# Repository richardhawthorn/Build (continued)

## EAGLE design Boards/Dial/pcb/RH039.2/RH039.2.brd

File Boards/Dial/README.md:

### Description

Dial board for use in build system

### Features

- Rotary encoder dial
- ATtiny44 processor
- DIL switch for 4 board addresses
- i2c communication with base
- 3.3v operation
- Surface mount

### License

This work is licensed under a Creative Commons Attribution-ShareAlike 4.0 International License.

<br />
Designed by <a xmlns:cc="http://creativecommons.org/ns#" href="http://www.richardhawthorn.com" property="cc:attributionName" rel="cc:attributionURL" target="_blank">Richard Hawthorn</a><br />
<a rel="license" href="http://creativecommons.org/licenses/by-sa/4.0/" target="_blank">View License</a>

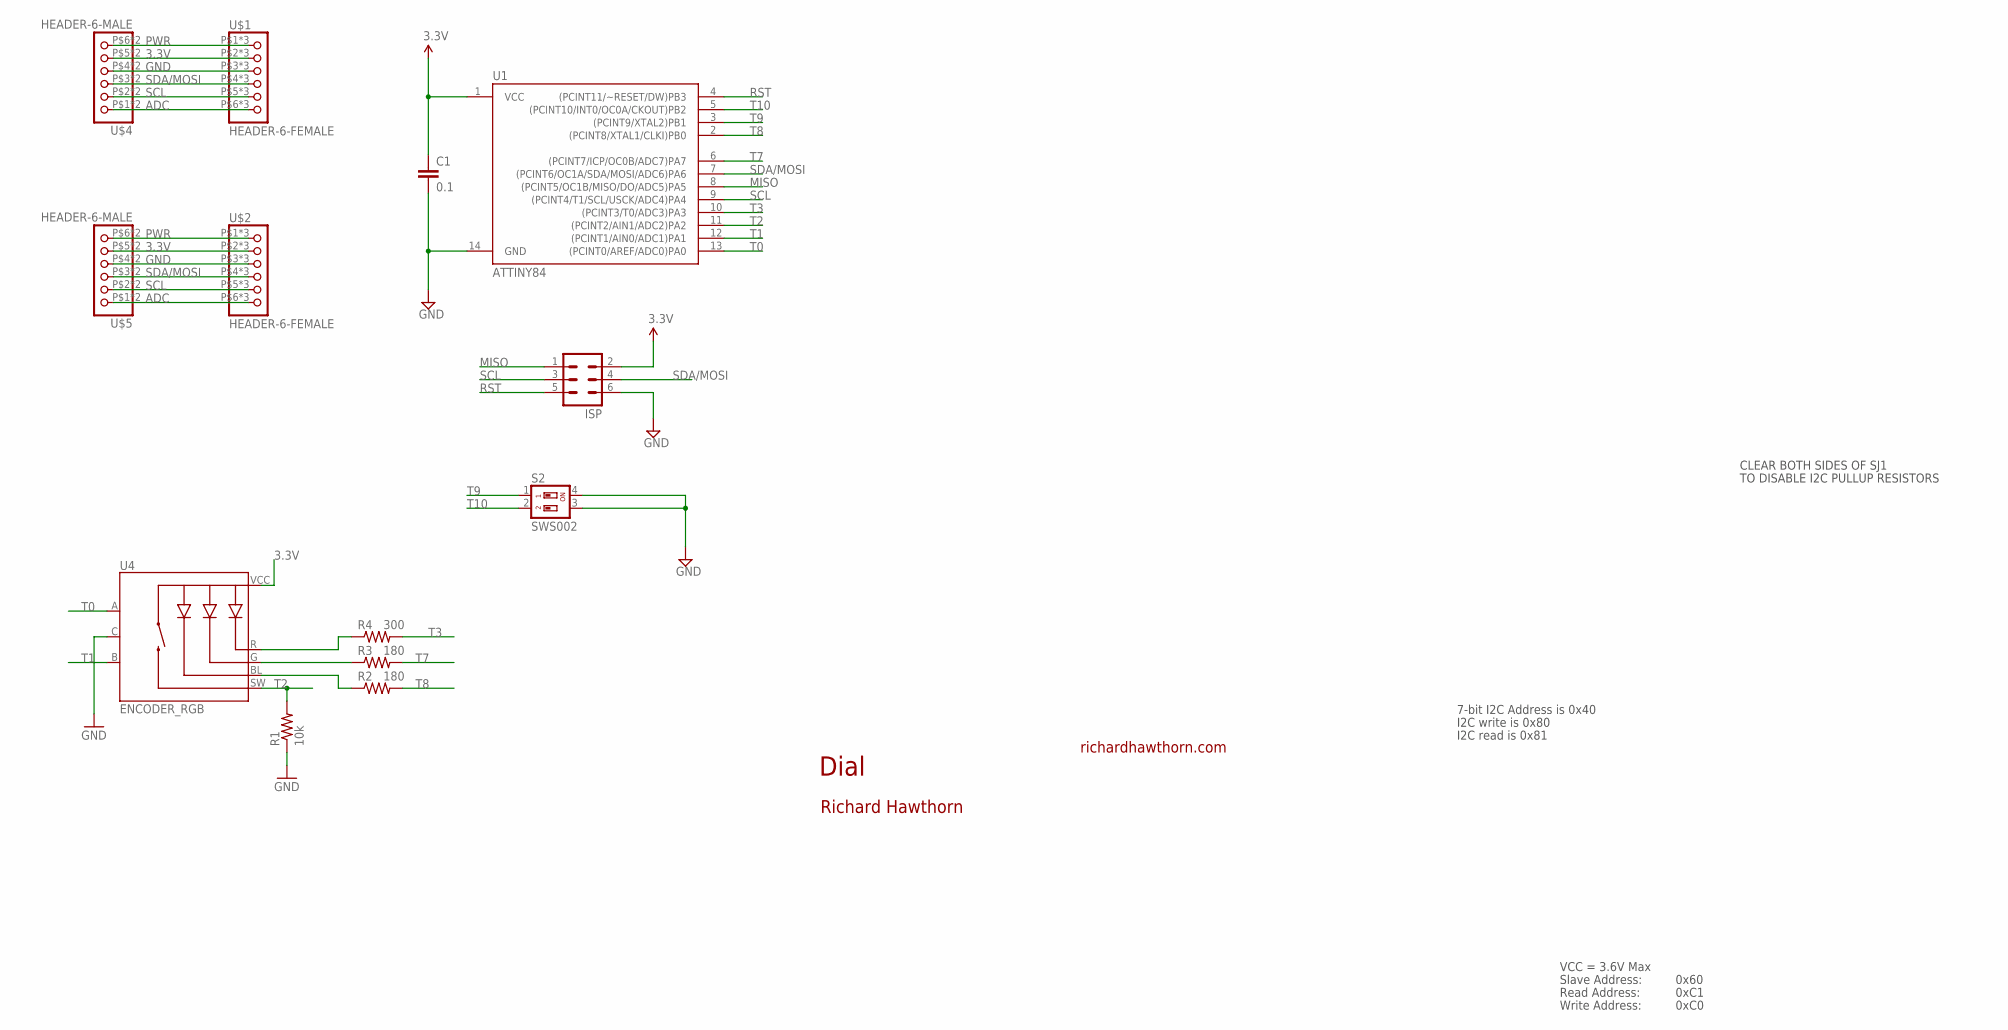
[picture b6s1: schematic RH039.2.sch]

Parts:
C1: 0.1; 0603-CAP
ISP: MA03-2
R1: 10k; 0402-RES
R2, R3: 180; 0402-RES
R4: 300; 0402-RES
S2: SWS002; SMS-002
U1: ATTINY84; SO14
U4: ENCODER_RGB; ENCODER_LED_RGB
U$1, U$2: HEADER-6-FEMALE; 2MMHEADER6
U$4, U$5: HEADER-6-MALE; 2MMHEADERPIN6

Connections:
3.3V: C1.1, ISP.2, U1.1 (VCC), U4.VCC, U$1.P$2 (2), U$1.P$10 (2), U$1.P$18 (2), U$2.P$2 (2), U$2.P$10 (2), U$2.P$18 (2), U$4.P$5 (5), U$4.P$13 (5), U$5.P$5 (5), U$5.P$13 (5)
ADC: U$1.P$6 (6), U$1.P$14 (6), U$1.P$22 (6), U$2.P$6 (6), U$2.P$14 (6), U$2.P$22 (6), U$4.P$1 (1), U$4.P$9 (1), U$5.P$1 (1), U$5.P$9 (1)
GND: C1.2, ISP.6, R1.1, S2.3, S2.4, U1.14 (GND), U4.C, U$1.P$3 (3), U$1.P$11 (3), U$1.P$19 (3), U$2.P$3 (3), U$2.P$11 (3), U$2.P$19 (3), U$4.P$4 (4), U$4.P$12 (4), U$5.P$4 (4), U$5.P$12 (4)
LED-B: R2.1, U4.BL
LED-G: R3.1, U4.G
LED-R: R4.1, U4.R
MISO: ISP.1, U1.8 ((PCINT5/OC1B/MISO/DO/ADC5)PA5)
PWR: U$1.P$1 (1), U$1.P$9 (1), U$1.P$17 (1), U$2.P$1 (1), U$2.P$9 (1), U$2.P$17 (1), U$4.P$6 (6), U$4.P$14 (6), U$5.P$6 (6), U$5.P$14 (6)
RST: ISP.5, U1.4 ((PCINT11/~RESET/DW)PB3)
SCL: ISP.3, U1.9 ((PCINT4/T1/SCL/USCK/ADC4)PA4), U$1.P$5 (5), U$1.P$13 (5), U$1.P$21 (5), U$2.P$5 (5), U$2.P$13 (5), U$2.P$21 (5), U$4.P$2 (2), U$4.P$10 (2), U$5.P$2 (2), U$5.P$10 (2)
SDA/MOSI: ISP.4, U1.7 ((PCINT6/OC1A/SDA/MOSI/ADC6)PA6), U$1.P$4 (4), U$1.P$12 (4), U$1.P$20 (4), U$2.P$4 (4), U$2.P$12 (4), U$2.P$20 (4), U$4.P$3 (3), U$4.P$11 (3), U$5.P$3 (3), U$5.P$11 (3)
T0: U1.13 ((PCINT0/AREF/ADC0)PA0), U4.A
T1: U1.12 ((PCINT1/AIN0/ADC1)PA1), U4.B
T2: R1.2, U1.11 ((PCINT2/AIN1/ADC2)PA2), U4.SW
T3: R4.2, U1.10 ((PCINT3/T0/ADC3)PA3)
T7: R3.2, U1.6 ((PCINT7/ICP/OC0B/ADC7)PA7)
T8: R2.2, U1.2 ((PCINT8/XTAL1/CLKI)PB0)
T9: S2.1, U1.3 ((PCINT9/XTAL2)PB1)
T10: S2.2, U1.5 ((PCINT10/INT0/OC0A/CKOUT)PB2)

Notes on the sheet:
Dial
richardhawthorn.com
Richard Hawthorn
CLEAR BOTH SIDES OF SJ1
TO DISABLE I2C PULLUP RESISTORS
7-bit I2C Address is 0x40
I2C write is 0x80
I2C read is 0x81
VCC = 3.6V Max
Read Address:
Write Address:
Slave Address:
0x60
0xC1
0xC0

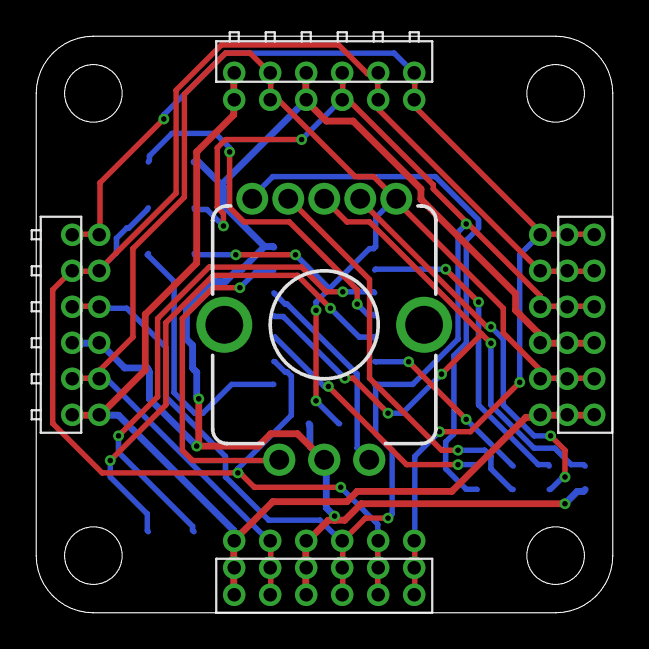
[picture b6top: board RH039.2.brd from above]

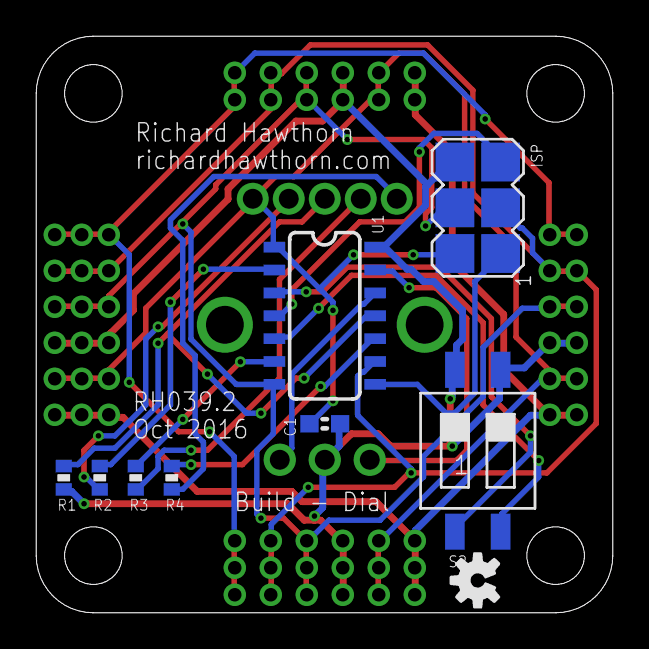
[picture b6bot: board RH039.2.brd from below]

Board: 2 copper layers, 32.0 x 32.0 mm, 14 parts (9 on the bottom side), 19 nets.

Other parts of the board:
U$3: OSHW-LOGO-S

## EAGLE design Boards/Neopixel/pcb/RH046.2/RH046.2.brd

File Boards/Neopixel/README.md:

### Description

Neopixel board for use in build system

### Features

- 2x2 Neopixels
- ATtiny44 processor
- DIL switch for 8 board addresses
- i2c communication with base
- 3.3v operation
- Surface mount

### License

This work is licensed under a Creative Commons Attribution-ShareAlike 4.0 International License.

<br />
Designed by <a xmlns:cc="http://creativecommons.org/ns#" href="http://www.richardhawthorn.com" property="cc:attributionName" rel="cc:attributionURL" target="_blank">Richard Hawthorn</a><br />
<a rel="license" href="http://creativecommons.org/licenses/by-sa/4.0/" target="_blank">View License</a>

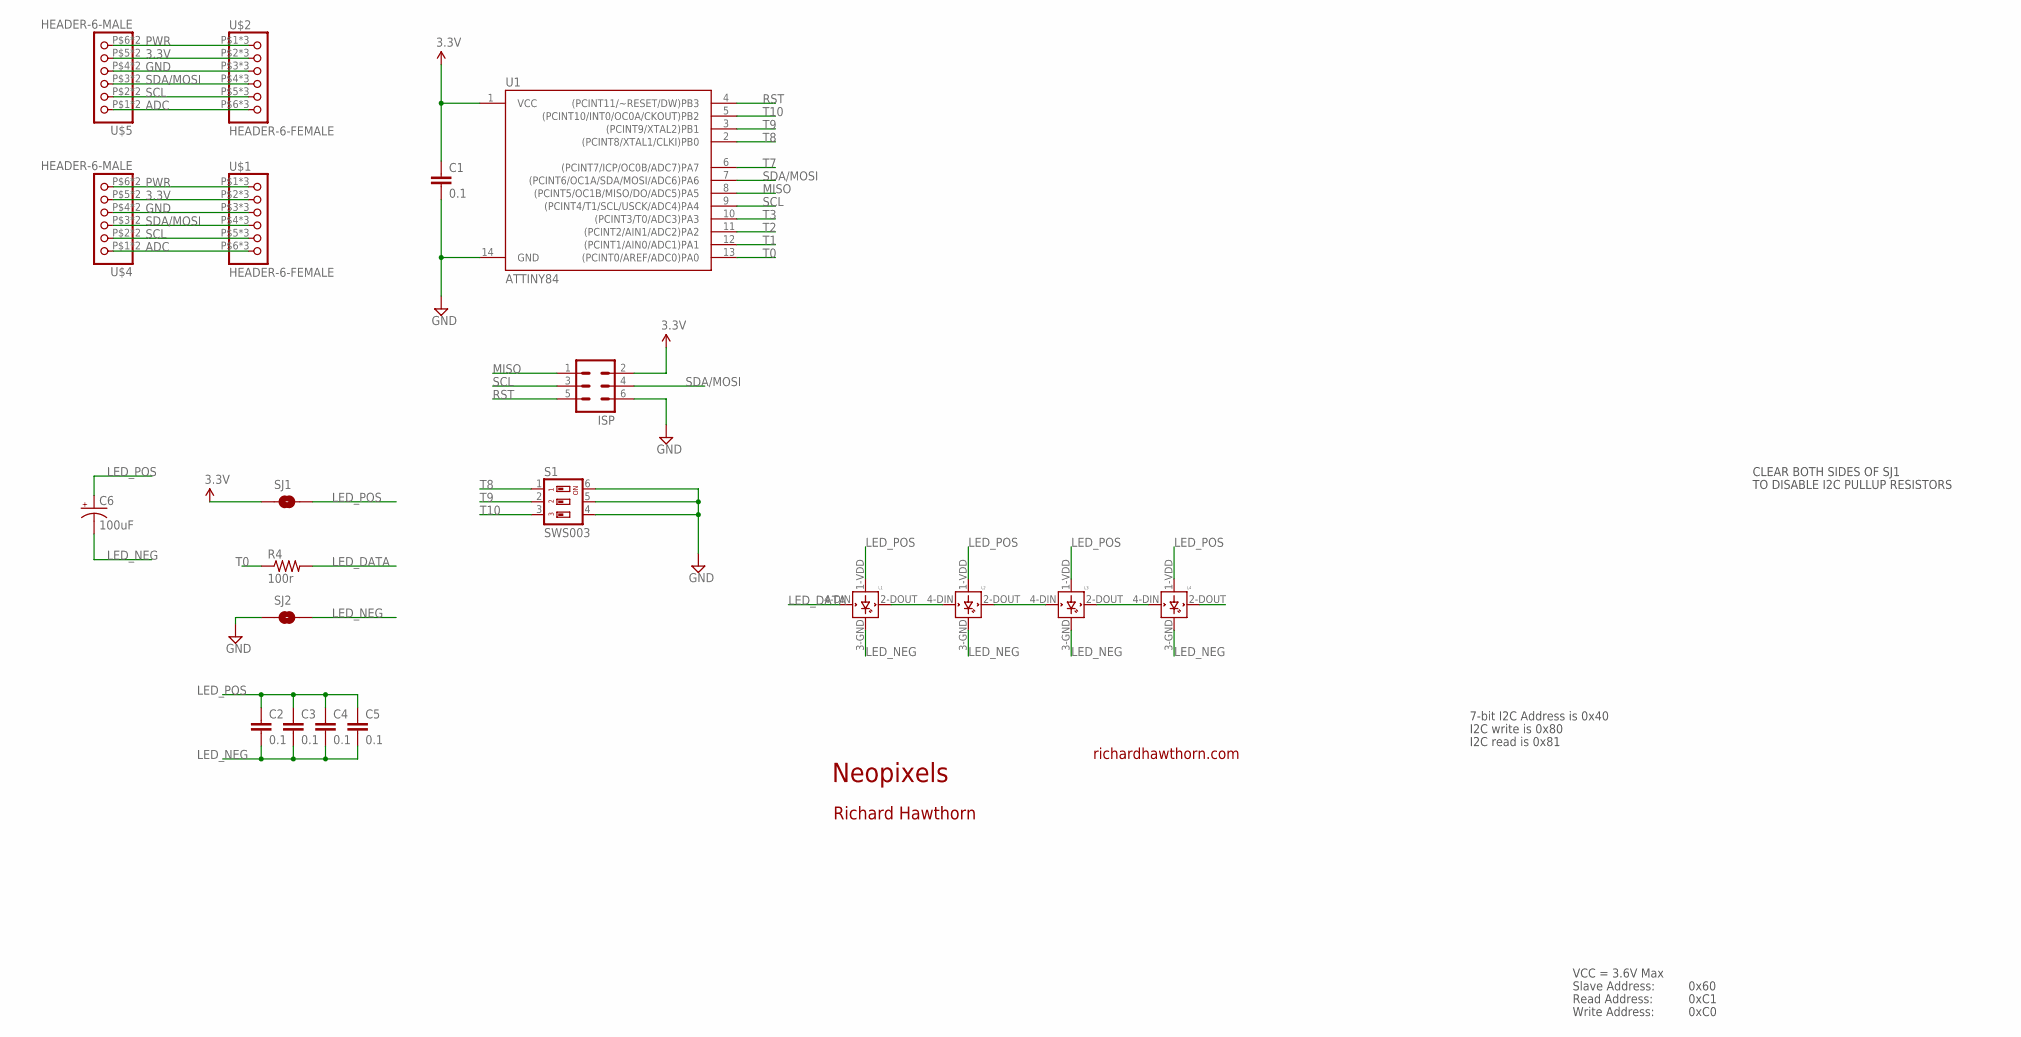
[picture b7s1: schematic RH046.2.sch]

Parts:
C1, C2, C3, C4, C5: 0.1; 0603-CAP
C6: 100uF; EIA7343
ISP: MA03-2
L1, L2, L3, L4: WS2812B
R4: 100r; 0603-RES
S1: SWS003; SMS-003
SJ1, SJ2: SOLDERJUMPERNO; SJ_2S-NO
U1: ATTINY84; SO14
U$1, U$2: HEADER-6-FEMALE; 2MMHEADER6
U$4, U$5: HEADER-6-MALE; 2MMHEADERPIN6

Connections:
3.3V: C1.1, ISP.2, SJ1.1, U1.1 (VCC), U$1.P$2 (2), U$1.P$10 (2), U$1.P$18 (2), U$2.P$2 (2), U$2.P$10 (2), U$2.P$18 (2), U$4.P$5 (5), U$4.P$13 (5), U$5.P$5 (5), U$5.P$13 (5)
ADC: U$1.P$6 (6), U$1.P$14 (6), U$1.P$22 (6), U$2.P$6 (6), U$2.P$14 (6), U$2.P$22 (6), U$4.P$1 (1), U$4.P$9 (1), U$5.P$1 (1), U$5.P$9 (1)
GND: C1.2, ISP.6, S1.4, S1.5, S1.6, SJ2.1, U1.14 (GND), U$1.P$3 (3), U$1.P$11 (3), U$1.P$19 (3), U$2.P$3 (3), U$2.P$11 (3), U$2.P$19 (3), U$4.P$4 (4), U$4.P$12 (4), U$5.P$4 (4), U$5.P$12 (4)
LED-OUT-1: L1.2-DOUT (DOUT), L2.4-DIN (DIN)
LED-OUT-2: L3.2-DOUT (DOUT), L4.4-DIN (DIN)
LED-OUT-3: L4.2-DOUT (DOUT)
LED_DATA: L1.4-DIN (DIN), R4.2
LED_NEG: C2.2, C3.2, C4.2, C5.2, C6.C (-), L1.3-GND (GND), L2.3-GND (GND), L3.3-GND (GND), L4.3-GND (GND), SJ2.2
LED_POS: C2.1, C3.1, C4.1, C5.1, C6.A (+), L1.1-VDD (VDD), L2.1-VDD (VDD), L3.1-VDD (VDD), L4.1-VDD (VDD), SJ1.2
MISO: ISP.1, U1.8 ((PCINT5/OC1B/MISO/DO/ADC5)PA5)
unnamed: L2.2-DOUT (DOUT), L3.4-DIN (DIN)
PWR: U$1.P$1 (1), U$1.P$9 (1), U$1.P$17 (1), U$2.P$1 (1), U$2.P$9 (1), U$2.P$17 (1), U$4.P$6 (6), U$4.P$14 (6), U$5.P$6 (6), U$5.P$14 (6)
RST: ISP.5, U1.4 ((PCINT11/~RESET/DW)PB3)
SCL: ISP.3, U1.9 ((PCINT4/T1/SCL/USCK/ADC4)PA4), U$1.P$5 (5), U$1.P$13 (5), U$1.P$21 (5), U$2.P$5 (5), U$2.P$13 (5), U$2.P$21 (5), U$4.P$2 (2), U$4.P$10 (2), U$5.P$2 (2), U$5.P$10 (2)
SDA/MOSI: ISP.4, U1.7 ((PCINT6/OC1A/SDA/MOSI/ADC6)PA6), U$1.P$4 (4), U$1.P$12 (4), U$1.P$20 (4), U$2.P$4 (4), U$2.P$12 (4), U$2.P$20 (4), U$4.P$3 (3), U$4.P$11 (3), U$5.P$3 (3), U$5.P$11 (3)
T0: R4.1, U1.13 ((PCINT0/AREF/ADC0)PA0)
T1: U1.12 ((PCINT1/AIN0/ADC1)PA1)
T2: U1.11 ((PCINT2/AIN1/ADC2)PA2)
T3: U1.10 ((PCINT3/T0/ADC3)PA3)
T7: U1.6 ((PCINT7/ICP/OC0B/ADC7)PA7)
T8: S1.1, U1.2 ((PCINT8/XTAL1/CLKI)PB0)
T9: S1.2, U1.3 ((PCINT9/XTAL2)PB1)
T10: S1.3, U1.5 ((PCINT10/INT0/OC0A/CKOUT)PB2)

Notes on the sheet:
Neopixels
richardhawthorn.com
Richard Hawthorn
CLEAR BOTH SIDES OF SJ1
TO DISABLE I2C PULLUP RESISTORS
7-bit I2C Address is 0x40
I2C write is 0x80
I2C read is 0x81
VCC = 3.6V Max
Read Address:
Write Address:
Slave Address:
0x60
0xC1
0xC0

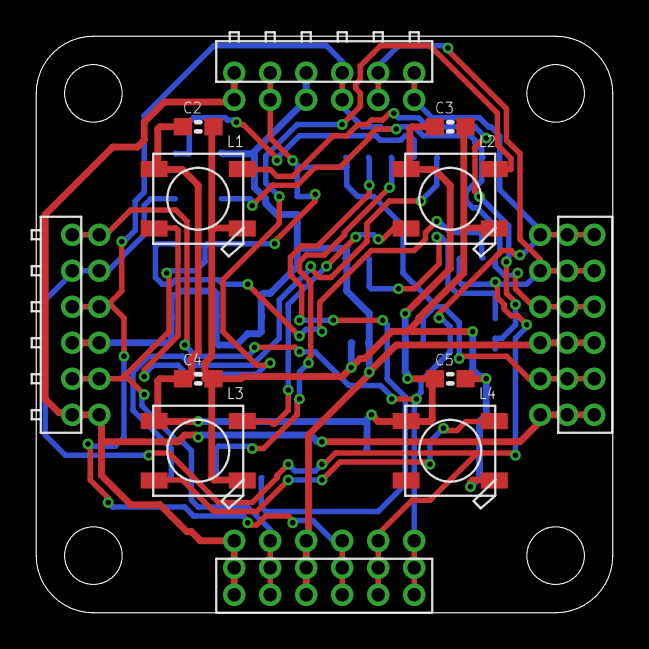
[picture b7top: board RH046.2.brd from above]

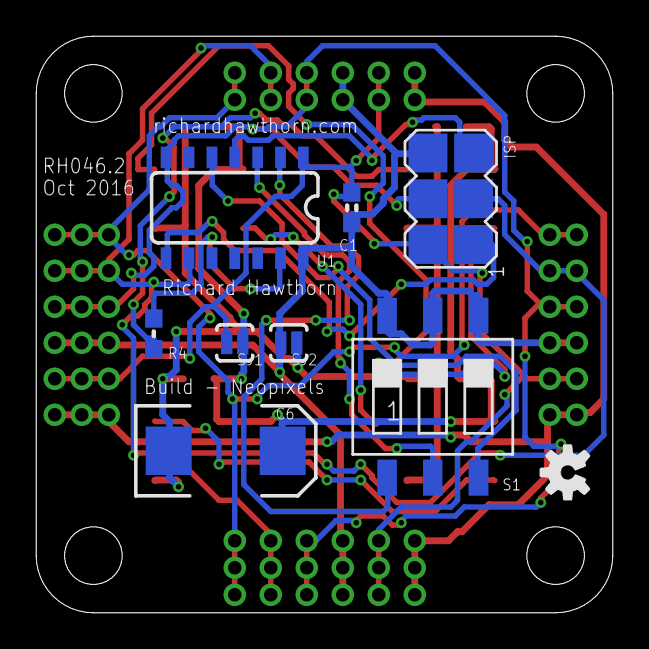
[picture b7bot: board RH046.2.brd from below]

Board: 2 copper layers, 32.0 x 32.0 mm, 21 parts (9 on the bottom side), 18 nets.

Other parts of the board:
U$3: OSHW-LOGO-S

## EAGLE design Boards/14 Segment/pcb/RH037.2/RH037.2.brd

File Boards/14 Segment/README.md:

### Description

14 segment LED screen for use in build system

### Features

- 14 Segment LED screen
- HT16K33 LED driver
- DIL switch for 8 board addresses
- i2c communication with base
- 3.3v operation
- Surface mount

### License

This work is licensed under a Creative Commons Attribution-ShareAlike 4.0 International License.

<br />
Designed by <a xmlns:cc="http://creativecommons.org/ns#" href="http://www.richardhawthorn.com" property="cc:attributionName" rel="cc:attributionURL" target="_blank">Richard Hawthorn</a><br />
<a rel="license" href="http://creativecommons.org/licenses/by-sa/4.0/" target="_blank">View License</a>

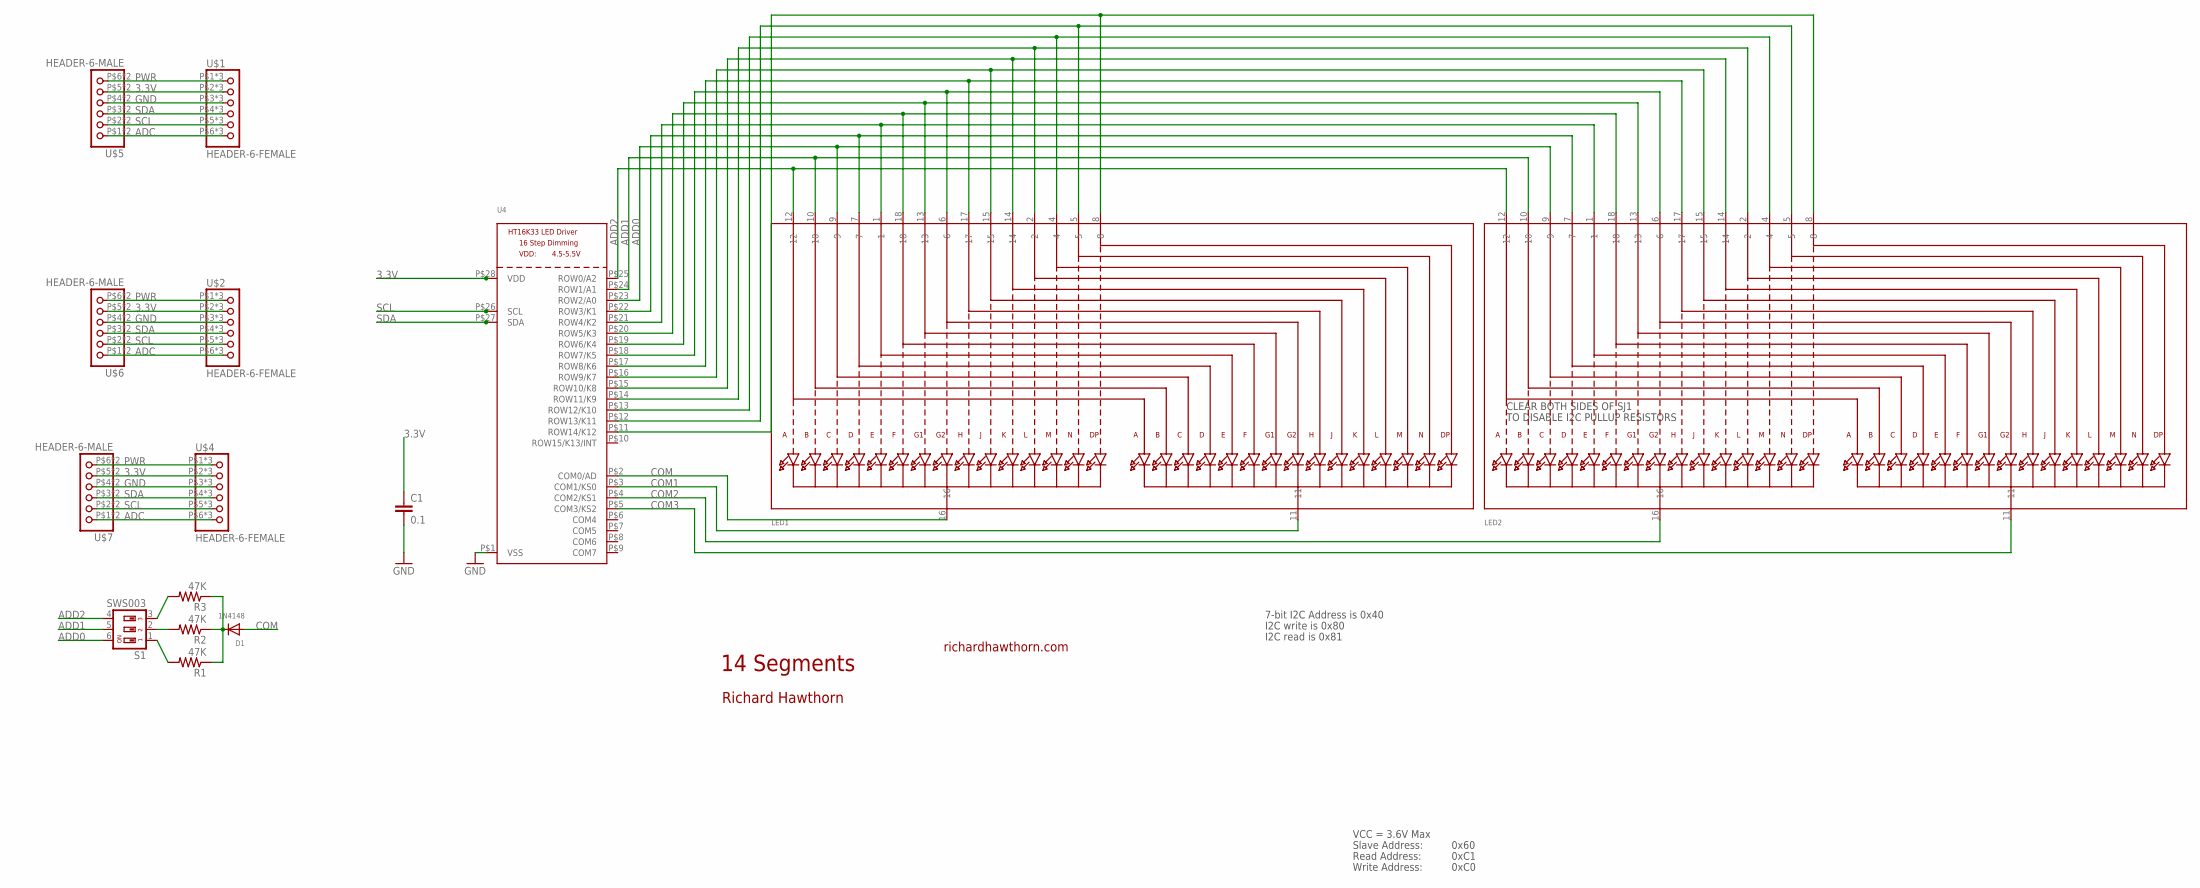
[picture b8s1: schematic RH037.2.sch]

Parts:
C1: 0.1; 0603-CAP
D1: 1N4148; SOD-323F
LED1, LED2: DISP_SEGMENT_STARBURST_DUAL_COMMONCATHODE; SEGMENT_STARTBUST_DUAL_KWA-541CBB
R1, R2, R3: 47K; R0805
S1: SWS003; SMS-003
U4: HT16K33_SOP28; SOP28_300MIL
U$1, U$2, U$4: HEADER-6-FEMALE; 2MMHEADER6
U$5, U$6, U$7: HEADER-6-MALE; 2MMHEADERPIN6

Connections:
3.3V: C1.1, U4.P$28 (VDD), U$1.P$2 (2), U$1.P$10 (2), U$1.P$18 (2), U$2.P$2 (2), U$2.P$10 (2), U$2.P$18 (2), U$4.P$2 (2), U$4.P$10 (2), U$4.P$18 (2), U$5.P$5 (5), U$5.P$13 (5), U$6.P$5 (5), U$6.P$13 (5), U$7.P$5 (5), U$7.P$13 (5)
ADC: U$1.P$6 (6), U$1.P$14 (6), U$1.P$22 (6), U$2.P$6 (6), U$2.P$14 (6), U$2.P$22 (6), U$4.P$6 (6), U$4.P$14 (6), U$4.P$22 (6), U$5.P$1 (1), U$5.P$9 (1), U$6.P$1 (1), U$6.P$9 (1), U$7.P$1 (1), U$7.P$9 (1)
ADD0: LED1.9, LED2.9, S1.6, U4.P$23 (ROW2/A0)
ADD1: LED1.10, LED2.10, S1.5, U4.P$24 (ROW1/A1)
ADD2: LED1.12, LED2.12, S1.4, U4.P$25 (ROW0/A2)
COM: D1.A, LED1.16, U4.P$2 (COM0/AD)
COM1: LED1.11, U4.P$3 (COM1/KS0)
COM2: LED2.16, U4.P$4 (COM2/KS1)
COM3: LED2.11, U4.P$5 (COM3/KS2)
GND: C1.2, U4.P$1 (VSS), U$1.P$3 (3), U$1.P$11 (3), U$1.P$19 (3), U$2.P$3 (3), U$2.P$11 (3), U$2.P$19 (3), U$4.P$3 (3), U$4.P$11 (3), U$4.P$19 (3), U$5.P$4 (4), U$5.P$12 (4), U$6.P$4 (4), U$6.P$12 (4), U$7.P$4 (4), U$7.P$12 (4)
unnamed: R3.2, S1.3
unnamed: D1.C, R1.1, R2.1, R3.1
unnamed: R1.2, S1.1
unnamed: R2.2, S1.2
unnamed: LED1.7, LED2.7, U4.P$22 (ROW3/K1)
unnamed: LED1.1, LED2.1, U4.P$21 (ROW4/K2)
unnamed: LED1.18, LED2.18, U4.P$20 (ROW5/K3)
unnamed: LED1.13, LED2.13, U4.P$19 (ROW6/K4)
unnamed: LED1.6, LED2.6, U4.P$18 (ROW7/K5)
unnamed: LED1.17, LED2.17, U4.P$17 (ROW8/K6)
unnamed: LED1.15, LED2.15, U4.P$16 (ROW9/K7)
unnamed: LED1.14, LED2.14, U4.P$15 (ROW10/K8)
unnamed: LED1.2, LED2.2, U4.P$14 (ROW11/K9)
unnamed: LED1.4, LED2.4, U4.P$13 (ROW12/K10)
unnamed: LED1.5, LED2.5, U4.P$12 (ROW13/K11)
unnamed: LED1.8, LED2.8, U4.P$11 (ROW14/K12)
PWR: U$1.P$1 (1), U$1.P$9 (1), U$1.P$17 (1), U$2.P$1 (1), U$2.P$9 (1), U$2.P$17 (1), U$4.P$1 (1), U$4.P$9 (1), U$4.P$17 (1), U$5.P$6 (6), U$5.P$14 (6), U$6.P$6 (6), U$6.P$14 (6), U$7.P$6 (6), U$7.P$14 (6)
SCL: U4.P$26 (SCL), U$1.P$5 (5), U$1.P$13 (5), U$1.P$21 (5), U$2.P$5 (5), U$2.P$13 (5), U$2.P$21 (5), U$4.P$5 (5), U$4.P$13 (5), U$4.P$21 (5), U$5.P$2 (2), U$5.P$10 (2), U$6.P$2 (2), U$6.P$10 (2), U$7.P$2 (2), U$7.P$10 (2)
SDA: U4.P$27 (SDA), U$1.P$4 (4), U$1.P$12 (4), U$1.P$20 (4), U$2.P$4 (4), U$2.P$12 (4), U$2.P$20 (4), U$4.P$4 (4), U$4.P$12 (4), U$4.P$20 (4), U$5.P$3 (3), U$5.P$11 (3), U$6.P$3 (3), U$6.P$11 (3), U$7.P$3 (3), U$7.P$11 (3)

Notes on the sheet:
14 Segments
richardhawthorn.com
Richard Hawthorn
CLEAR BOTH SIDES OF SJ1
TO DISABLE I2C PULLUP RESISTORS
7-bit I2C Address is 0x40
I2C write is 0x80
I2C read is 0x81
VCC = 3.6V Max
Read Address:
Write Address:
Slave Address:
0x60
0xC1
0xC0

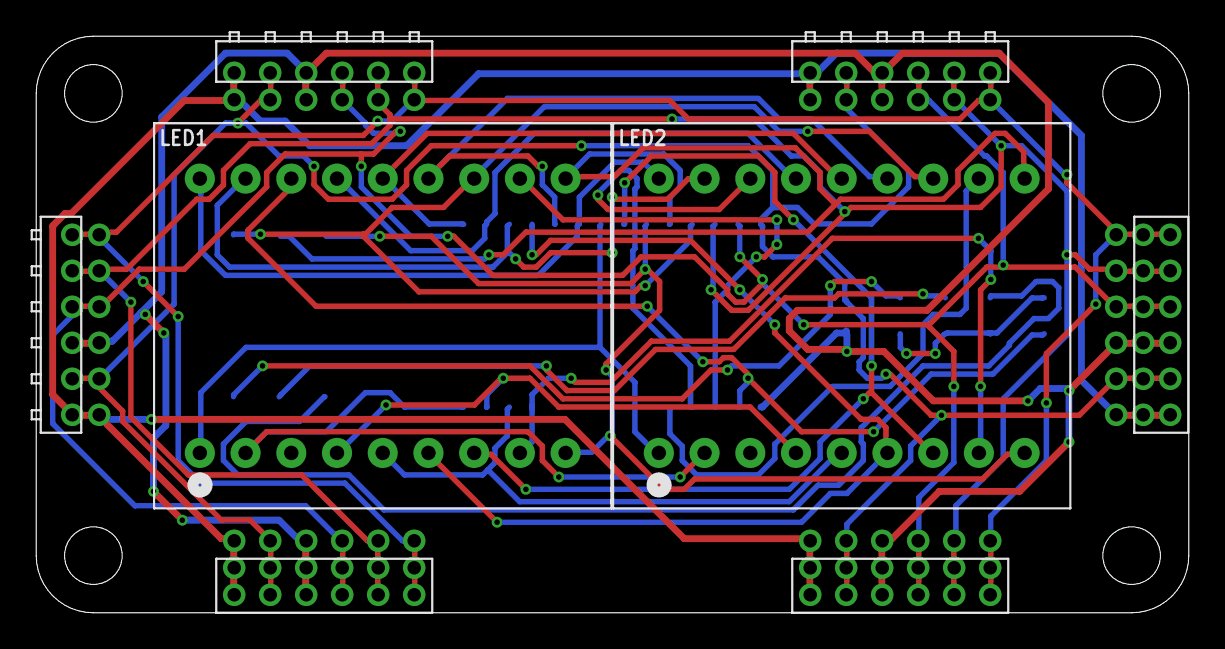
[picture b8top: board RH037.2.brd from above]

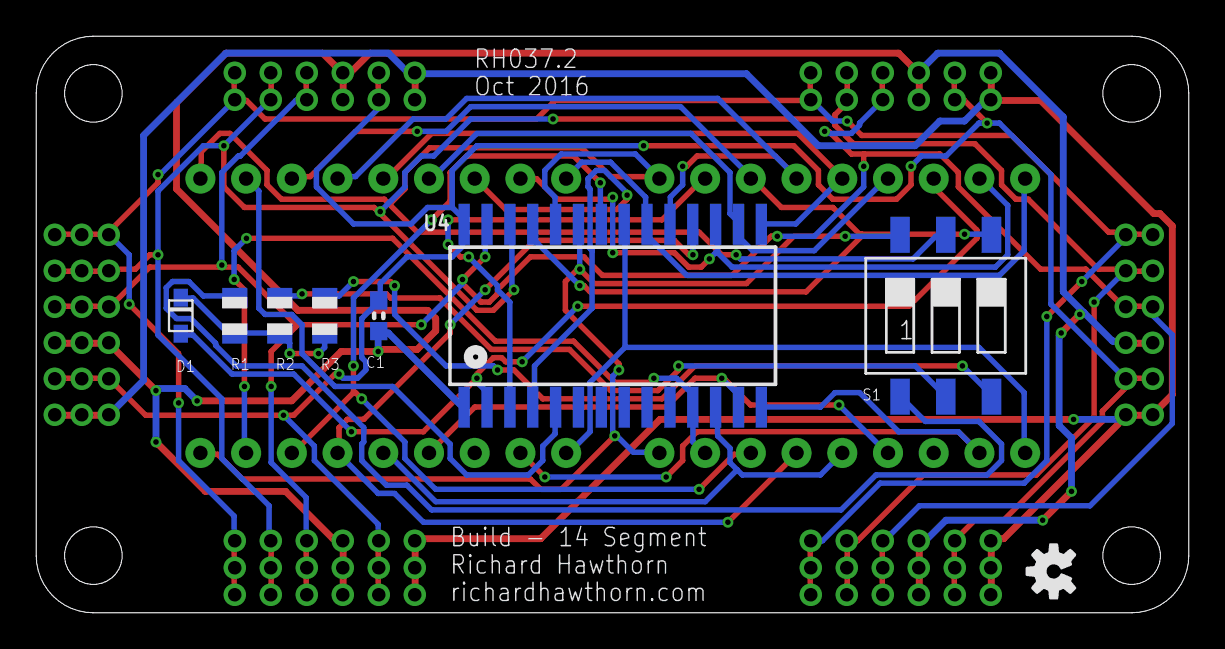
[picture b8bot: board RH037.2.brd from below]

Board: 2 copper layers, 64.0 x 32.0 mm, 16 parts (8 on the bottom side), 29 nets.

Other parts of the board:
U$3: OSHW-LOGO-S

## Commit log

2018-01-28 add readme
2018-01-28 add boards
2018-01-28 add pcb images
2018-01-28 add readme files
2018-01-28 update images for button board
2018-01-28 update readme files
2018-01-29 add images
